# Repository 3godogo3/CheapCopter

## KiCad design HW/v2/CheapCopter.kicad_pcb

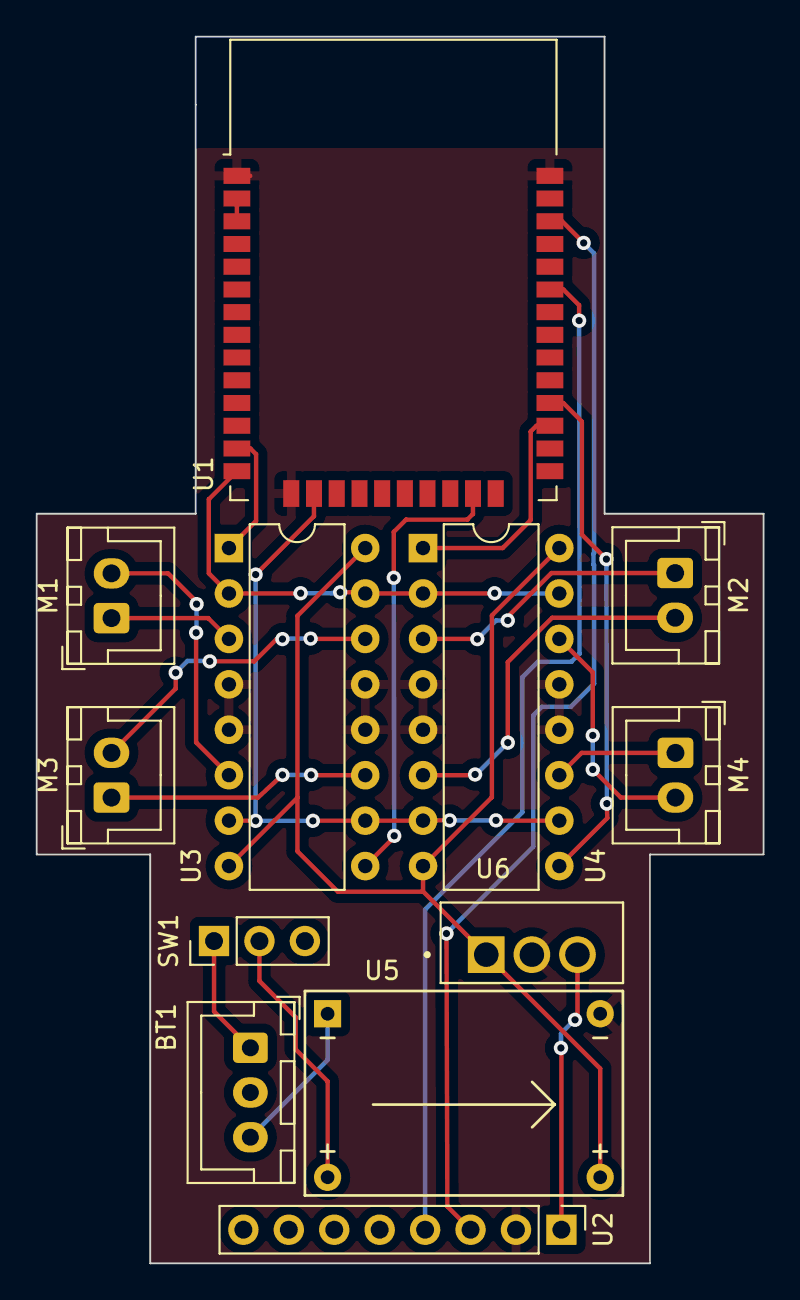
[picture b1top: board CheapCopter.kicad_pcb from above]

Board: 2 copper layers, 40.6 x 68.6 mm, 12 parts (0 on the bottom side), 23 nets.

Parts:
BT1: 7.4V; JST_XH_B3B-XH-A_1x03_P2.50mm_Vertical
M1, M2, M3, M4: 3-5V; JST_XH_B2B-XH-A_1x02_P2.50mm_Vertical
SW1: PinHeader_1x03_P2.54mm_Vertical
U1: ESP32-WROOM-32
U2: MPU-6050; PinHeader_1x08_P2.54mm_Vertical
U3, U4: L293D; DIP-16_W7.62mm
U5: Mini360_Module
U6: L7805; TO255P1020X450X2000-3

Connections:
+3.3V: U2.1 (CLKIN), U6.3 (OUT)
+3V3: U1.2 (VDD), U1.3 (EN)
+5V: U3.8 (VCC2), U3.16 (VCC1), U4.8 (VCC2), U4.16 (VCC1), U5.3 (OUT+), U6.1 (IN)
EN1: U1.13 (IO14), U3.1 (EN1,2)
EN2: U1.27 (IO16), U4.1 (EN1,2)
EN3: U1.23 (IO15), U3.9 (EN3,4)
EN4: U1.28 (IO17), U4.9 (EN3,4)
GND: U1.1 (GND), U1.15 (GND), U1.38 (GND), U2.2 (NC), U3.4 (GND), U3.5 (GND), U3.12 (GND), U3.13 (GND), U4.4 (GND), U4.5 (GND), U4.12 (GND), U4.13 (GND), U5.4 (OUT-), U6.2 (GND)
M_HIGH: U1.14 (IO12), U3.2 (1A), U3.15 (4A), U4.2 (1A), U4.15 (4A)
M_LOW: U1.16 (IO13), U3.7 (2A), U3.10 (3A), U4.7 (2A), U4.10 (3A)
unnamed: BT1.1 (+), SW1.1 (A)
unnamed: BT1.3, U5.2 (IN-)
unnamed: M1.1 (+), U3.3 (1Y)
unnamed: M1.2 (-), U3.6 (2Y)
unnamed: M2.1 (+), U4.3 (1Y)
unnamed: M2.2 (-), U4.6 (2Y)
unnamed: M3.1 (+), U3.11 (3Y)
unnamed: M3.2 (-), U3.14 (4Y)
unnamed: M4.1 (+), U4.11 (3Y)
unnamed: M4.2 (-), U4.14 (4Y)
unnamed: SW1.2 (B), U5.1 (IN+)
SCL: U1.36 (IO22), U2.3 (NC)
SDA: U1.33 (IO21), U2.4 (NC)

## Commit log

2023-10-31 First circuit schematic and pcb file
2024-01-24 First code
    Added code for WiFi AP, OTA and basic wireless controlling
2024-01-24 Update dron.ino
    removed typo
2024-02-26 v2
    added v2 pcb files
2024-02-28 Code Update
    Added missing commands
    Changed serial connection to telnet
    Added selfbalancing
2024-03-02 Documentation added
2024-03-02 Create LICENSE
2024-03-02 Typo correction
2024-03-02 Body model v2
2024-03-20 replace telnet with web ui
2024-03-21 Changed doc template
2024-03-21 Add tex package to template
2024-03-21 Updated documentation
